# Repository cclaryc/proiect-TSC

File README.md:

# Overview - Hector Watch

Proiectul **Hector Watch** vizează dezvoltarea unui smartwatch, optimizat pentru consum redus de energie. Sistemul este construit în jurul microcontrolerului **nRF52840** și utilizează un afișaj de tip **e-Paper** de 1.54 inch.

### 1. Arhitectura Hardware și Selecția Componentelor
Această etapă a constat în definirea specificațiilor și alegerea componentelor pentru eficiență energetică maximă:
* **Unitate centrală:** nRF52840 (SoC cu suport BLE 5.3).
* **Afișaj:** Panou E-Ink Waveshare 1.54".
* **Senzori și Feedback:** Accelerometru Bosch BMA423 (I2C) și driver haptic TI DRV2605.
* **Sursă de energie:** Baterie Li-Po 250mAh .

## Functional Architecture

Arhitectura funcțională este proiectată pentru a maximiza eficiența energetică și a asigura o comunicare fluidă între procesorul central și perifericele specializate.

### 1. Sistemul de Management al Energiei (PMU)
Acest subsistem asigură alimentarea continuă și protecția circuitelor:
* **Input:** USB-C (5V) pentru încărcare.
* **Încărcare și Protecție:** Realizată prin IC1 , care gestionează ciclul de încărcare al bateriei Li-Po.
* **Monitorizare (Fuel Gauge): U3 raportează starea de încărcare (SoC) și tensiunea bateriei prin I2C.
* **Reglare:** IC2 (Buck-Boost) transformă tensiunea variabilă a bateriei într-o tensiune stabilă de **3.3V** pentru restul componentelor.

### 2. Procesare și Conectivitate
* **Core:** **nRF52840** (ARM Cortex-M4F) rulează logica ceasului și gestionează stack-ul de Bluetooth Low Energy (BLE).
* **Timing:** Cristale externe de 32MHz (precizie procesor) și 32.768kHz (precizie ceas/RTC în mod sleep).

### 3. Interfața Om-Mașină (HMI)
* **Output Vizual:** Ecranul **E-Ink** (cerneală electronică) reține imaginea fără consum de curent, fiind actualizat prin protocolul **SPI**. 
* **Output Haptic:** Driver-ul U2 traduce comenzile I2C în vibrații mecanice prin motorul de tip coin.
* **Input:** Trei butoane fizice (GPIO) pentru navigare și interacțiune.

### 4. Subsistemul de Senzori
* Accelerometrul **BMA423** monitorizează activitatea fizică și detectează orientarea încheieturii pentru activarea ecranului.

### Block Diagram

### Matricea de Comunicație (Data Bus)

| Bus | Periferic | Tip | Rol |
| :--- | :--- | :--- | :--- |
| **SPI** | E-Paper Display | Master -> Slave | Transfer rapid de buffere de imagine |
| **I2C** | BMA423, DRV2605, MAX17048, BQ25180 | Multimaster | Configurare senzori și citire telemetrie baterie |
| **GPIO** | Butoane, Display Power (PFET), Motor EN | Digital I/O | Control direct și evenimente asincrone |

### Bill of Materials

| Referință | Componentă | Funcție | Package | JLC Code | Datasheet |
| :--- | :--- | :--- | :--- | :--- | :--- |
| **IC1 (U1)** | nRF52840-QIAA | Procesor principal (MCU) și controller Bluetooth. | aQFN73 | C190740 | [Link](https://jlcpcb.com/api/file/downloadByFileSystemAccessId/8588884082339532800) |
| **IC2 (U2)** | BQ25180YBGR | Încărcător de baterie inteligent. | WLCSP-8 | C2907431 | [Link](https://www.ti.com/cn/lit/gpn/bq25180) |
| **IC3 (U3)** | MAX17048G+T10 | Monitorizează nivelul bateriei (Fuel Gauge). | TDFN-8 | C72035 | [Link](https://jlc-prod-smt.oss-eu-central-1.aliyuncs.com/smtDataManualFile/8588907428515614720-C2682616.pdf?response-content-disposition=attachment%3B%20filename%3DC2682616.pdf%3B%20filename%2A%3DUTF-8%27%27C2682616.pdf&x-oss-date=20260421T112544Z&x-oss-expires=1800&x-oss-security-token=CAISgAN1q6Ft5B2yfSjIr5n4OcKMmaVj5%2FfYekzrr2IHQf9m3ZfGjzz2IHhMdHJsAOodtv0%2FmmhT6PkclqRLcbhpcmfjV%2BZHzLB8qcVSq2Ny4J7b16cNrbH4M4H6aXeirtuwDsz9SNTCALjPD3nPii50x5bjaDymRCbLGJaViJlhHLN1Ow6jdmhpCctxLAlvo9NgFxm3D%2Fu2NQPwiWf9FVdhvhEG6Vly8qOi2MaRmFy8yFTx0b0SvJ%2BjYMrmPctoN9JnSdC5mfdzau3a1TJ84gRD0a5wkaVA1zbDs5bfISEIuUzebreLqY03dV4mOvdqIcMe8qigz88fk%2FfIioH6xyxKOexoSCnFTOiiupCcQLPyao9jLu6iayqViY7QaIOTqQohZmkAMwVOasAsI3Ngh4zF97Qt0cVNkXO9gWfLI8DtuMleWqrqV%2FhfznSgc5lCkRRYwGs1287ugXlSQzo890KPDAEovaKCnZ2ZSfh7Y4sNknI6i%2Bfc2Se2MIkIzFMa4qKWD5sagAGLzp3fHP9zsDxV2%2FJMGJhYD%2FSIjxpKz7fqt2nFmhY%2BY1WslVCo8Aeg8t%2FASS7YFDik2EKmA7r2Qpp7S9DhCxHh3UmkIh5jq2t2qTGkqx1qYPq5E3JFwFQNyBq2LNYj5F%2B%2BlRwX66i2djJKGm9qTW%2FuuXCYOKChaO82y5rYRjpzLyAA&x-oss-signature-version=OSS4-HMAC-SHA256&x-oss-credential=STS.NZMrx8tzBP53xjZKbRMpJ2Rmm%2F20260421%2Feu-central-1%2Foss%2Faliyun_v4_request&x-oss-signature=e0bf51dc5869d52ac2c81a85deb4332a4d147174e99a754ec8a8e7ac85831cb3) |
| **IC4 (U4)** | DRV2605YZFR | Driver specializat pentru efecte haptice. | BGA-9 | C156475 | [Link](https://www.ti.com/cn/lit/gpn/drv2605) |
| **IC5 (U5)** | BMA423 | Senzor de mișcare (pași/gesturi). | LGA-12 | C406450 | [Link](https://jlc-prod-smt.oss-eu-central-1.aliyuncs.com/smtDataManualFile/8588894317138628608-C189517.pdf?response-content-disposition=attachment%3B%20filename%3DC189517.pdf%3B%20filename%2A%3DUTF-8%27%27C189517.pdf&x-oss-date=20260421T112629Z&x-oss-expires=1800&x-oss-security-token=CAISgAN1q6Ft5B2yfSjIr5n4OcKMmaVj5%2FfYekzrr2IHQf9m3ZfGjzz2IHhMdHJsAOodtv0%2FmmhT6PkclqRLcbhpcmfjV%2BZHzLB8qcVSq2Ny4J7b16cNrbH4M4H6aXeirtuwDsz9SNTCALjPD3nPii50x5bjaDymRCbLGJaViJlhHLN1Ow6jdmhpCctxLAlvo9NgFxm3D%2Fu2NQPwiWf9FVdhvhEG6Vly8qOi2MaRmFy8yFTx0b0SvJ%2BjYMrmPctoN9JnSdC5mfdzau3a1TJ84gRD0a5wkaVA1zbDs5bfISEIuUzebreLqY03dV4mOvdqIcMe8qigz88fk%2FfIioH6xyxKOexoSCnFTOiiupCcQLPyao9jLu6iayqViY7QaIOTqQohZmkAMwVOasAsI3Ngh4zF97Qt0cVNkXO9gWfLI8DtuMleWqrqV%2FhfznSgc5lCkRRYwGs1287ugXlSQzo890KPDAEovaKCnZ2ZSfh7Y4sNknI6i%2Bfc2Se2MIkIzFMa4qKWD5sagAGLzp3fHP9zsDxV2%2FJMGJhYD%2FSIjxpKz7fqt2nFmhY%2BY1WslVCo8Aeg8t%2FASS7YFDik2EKmA7r2Qpp7S9DhCxHh3UmkIh5jq2t2qTGkqx1qYPq5E3JFwFQNyBq2LNYj5F%2B%2BlRwX66i2djJKGm9qTW%2FuuXCYOKChaO82y5rYRjpzLyAA&x-oss-signature-version=OSS4-HMAC-SHA256&x-oss-credential=STS.NZMrx8tzBP53xjZKbRMpJ2Rmm%2F20260421%2Feu-central-1%2Foss%2Faliyun_v4_request&x-oss-signature=1b2c6936aa63600c7496d9337576edecc9ae5bf56b8ef562c67036a6727a361c) |
| **IC6 (U6)** | RT6160AWSC | Regulator Buck-Boost (3.3V stabil). | WLCSP-15 | C141692 | [Link](https://jlcpcb.com/api/file/downloadByFileSystemAccessId/8600398231234883584) |
| **IC7 (U7)** | USBLC6-2SC6Y | Protecție ESD la mufa USB. | SOT-23-6L | C7519 | [Link](https://jlc-prod-smt.oss-eu-central-1.aliyuncs.com/smtDataManualFile/8603165824283140096-C2969755.pdf?response-content-disposition=attachment%3B%20filename%3DC2969755.pdf%3B%20filename%2A%3DUTF-8%27%27C2969755.pdf&x-oss-date=20260421T112712Z&x-oss-expires=1800&x-oss-security-token=CAISgAN1q6Ft5B2yfSjIr5n4OcKMmaVj5%2FfYekzrr2IHQf9m3ZfGjzz2IHhMdHJsAOodtv0%2FmmhT6PkclqRLcbhpcmfjV%2BZHzLB8qcVSq2Ny4J7b16cNrbH4M4H6aXeirtuwDsz9SNTCALjPD3nPii50x5bjaDymRCbLGJaViJlhHLN1Ow6jdmhpCctxLAlvo9NgFxm3D%2Fu2NQPwiWf9FVdhvhEG6Vly8qOi2MaRmFy8yFTx0b0SvJ%2BjYMrmPctoN9JnSdC5mfdzau3a1TJ84gRD0a5wkaVA1zbDs5bfISEIuUzebreLqY03dV4mOvdqIcMe8qigz88fk%2FfIioH6xyxKOexoSCnFTOiiupCcQLPyao9jLu6iayqViY7QaIOTqQohZmkAMwVOasAsI3Ngh4zF97Qt0cVNkXO9gWfLI8DtuMleWqrqV%2FhfznSgc5lCkRRYwGs1287ugXlSQzo890KPDAEovaKCnZ2ZSfh7Y4sNknI6i%2Bfc2Se2MIkIzFMa4qKWD5sagAGLzp3fHP9zsDxV2%2FJMGJhYD%2FSIjxpKz7fqt2nFmhY%2BY1WslVCo8Aeg8t%2FASS7YFDik2EKmA7r2Qpp7S9DhCxHh3UmkIh5jq2t2qTGkqx1qYPq5E3JFwFQNyBq2LNYj5F%2B%2BlRwX66i2djJKGm9qTW%2FuuXCYOKChaO82y5rYRjpzLyAA&x-oss-signature-version=OSS4-HMAC-SHA256&x-oss-credential=STS.NZMrx8tzBP53xjZKbRMpJ2Rmm%2F20260421%2Feu-central-1%2Foss%2Faliyun_v4_request&x-oss-signature=3bd40d510d9216cc6425f6a729325acb3ecaeffaa7238b5506b9054adb73b786) |
| **X1** | ECS-320-10-33B | Cristal 32MHz pentru Bluetooth. | 3225 SMD | C110292 | [Link](https://www.google.com/search?q=https://ecsxtal.com/store/pdf/ECS-320-10-33B-CKM.pdf) |
| **X2** | NX3215SA | Cristal 32.768kHz pentru RTC. | 3215 SMD | C32156 | [Link](https://www.ndk.com/images/products/catalog/c_NX3215SA_e.pdf) |
| **D1** | MBR0530 | Diodă Schottky pentru protecție curent. | SOD-123 | C8200 | [Link](https://www.onsemi.com/pdf/datasheet/mbr0530t1-d.pdf) |
| **D2-D5** | Generic 0402 | LED-uri stare (încărcare/notificări). | 0402 SMD | - | - |
| **L1** | MLP2016H2R2MT | Inductor Power pentru RT6160. | 2016 SMD | C135431 | [Link](https://product.tdk.com/system/files/dam/doc/product/inductor/inductor/smd/catalog/inductor_commercial_power_mlp2016_en.pdf) |
| **Q1** | SI1308EDL | Switch logic pentru alimentare display. | SOT-23 | C140222 | [Link](https://www.vishay.com/docs/63399/si1308edl.pdf) |
| **Resistors** | C3920633 | Pull-up I2C și limitare LED. | 0201 | **C3920633** | - |
| **Capacitors**| C9900156064 | Filtrare și decuplare generală. | 0201 | **C9900156064** | - |
| **C23, 27..** | C21012218 | Stabilitate tensiune. | - | **C21012218** | - |
| **C24, 25..** | C9900179830 | Filtrare intrare/ieșire putere. | 0402 | **C9900179830** | - |
| **DISP** | Waveshare 1.54" | Ecran principal E-Ink. | 37.3x31.8 mm | - | [Link PDF](https://www.waveshare.com/w/upload/7/77/1.54inch_e-Paper_Datasheet.pdf?srsltid=AfmBOorvr9QUc2F2yPCG9JTKScM4Ca_KRrmOvzZPdTIs-fBF9CH1EZh_) |
| **BATT** | Akyga LP502030 | Sursă energie (250mAh). | 32.5x21 mm | - | [Link](https://files.elektroniksc.com.pl/14017-2427914986/LP502030.pdf) |
| **MOT** | FIT0774 | Motor vibrații haptic. | Ø10 x 3 mm | - | [Link](https://jlc-prod-smt.oss-eu-central-1.aliyuncs.com/smtDataManualFile/8600542373223424000-C17569954.pdf?response-content-disposition=attachment%3B%20filename%3DC17569954.pdf%3B%20filename%2A%3DUTF-8%27%27C17569954.pdf&x-oss-date=20260421T113148Z&x-oss-expires=1800&x-oss-security-token=CAISgAN1q6Ft5B2yfSjIr5n4OcKMmaVj5%2FfYekzrr2IHQf9m3ZfGjzz2IHhMdHJsAOodtv0%2FmmhT6PkclqRLcbhpcmfjV%2BZHzLB8qcVSq2Ny4J7b16cNrbH4M4H6aXeirtuwDsz9SNTCALjPD3nPii50x5bjaDymRCbLGJaViJlhHLN1Ow6jdmhpCctxLAlvo9NgFxm3D%2Fu2NQPwiWf9FVdhvhEG6Vly8qOi2MaRmFy8yFTx0b0SvJ%2BjYMrmPctoN9JnSdC5mfdzau3a1TJ84gRD0a5wkaVA1zbDs5bfISEIuUzebreLqY03dV4mOvdqIcMe8qigz88fk%2FfIioH6xyxKOexoSCnFTOiiupCcQLPyao9jLu6iayqViY7QaIOTqQohZmkAMwVOasAsI3Ngh4zF97Qt0cVNkXO9gWfLI8DtuMleWqrqV%2FhfznSgc5lCkRRYwGs1287ugXlSQzo890KPDAEovaKCnZ2ZSfh7Y4sNknI6i%2Bfc2Se2MIkIzFMa4qKWD5sagAGLzp3fHP9zsDxV2%2FJMGJhYD%2FSIjxpKz7fqt2nFmhY%2BY1WslVCo8Aeg8t%2FASS7YFDik2EKmA7r2Qpp7S9DhCxHh3UmkIh5jq2t2qTGkqx1qYPq5E3JFwFQNyBq2LNYj5F%2B%2BlRwX66i2djJKGm9qTW%2FuuXCYOKChaO82y5rYRjpzLyAA&x-oss-signature-version=OSS4-HMAC-SHA256&x-oss-credential=STS.NZMrx8tzBP53xjZKbRMpJ2Rmm%2F20260421%2Feu-central-1%2Foss%2Faliyun_v4_request&x-oss-signature=3123648a1255a4bcd5d4fe98690891d424c0b7d99660a32dc277129baedf181c) |
| **USB** | KH-TYPE-C-16P | Port încărcare și date USB-C. | 16-pin SMD | C165948 | [Link](https://www.snapeda.com/parts/KH-TYPE-C-16P/kinghelm/datasheet/) |
| **J1** | 503480-2400 | Conector FPC (Display). | 0.5mm Pitch | C262524 | [Link](https://www.molex.com/en-us/products/part-detail/5034802400) |
| **ANT** | 2450AT18B100E | Antenă Bluetooth 2.4GHz. | 3216 SMD | C105151 | [Link](https://www.johansontechnology.com/datasheets/2450AT18B100.pdf) |
| **BTN** | EVP-AKE31A | Butoane navigare meniu. | 3.8x1.9 mm | C138127 | [Link](hhttps://jlc-prod-smt.oss-eu-central-1.aliyuncs.com/smtDataManualFile/8588931144787611648-C569760.pdf?response-content-disposition=attachment%3B%20filename%3DC569760.pdf%3B%20filename%2A%3DUTF-8%27%27C569760.pdf&x-oss-date=20260421T113342Z&x-oss-expires=1800&x-oss-security-token=CAISgAN1q6Ft5B2yfSjIr5n4OcKMmaVj5%2FfYekzrr2IHQf9m3ZfGjzz2IHhMdHJsAOodtv0%2FmmhT6PkclqRLcbhpcmfjV%2BZHzLB8qcVSq2Ny4J7b16cNrbH4M4H6aXeirtuwDsz9SNTCALjPD3nPii50x5bjaDymRCbLGJaViJlhHLN1Ow6jdmhpCctxLAlvo9NgFxm3D%2Fu2NQPwiWf9FVdhvhEG6Vly8qOi2MaRmFy8yFTx0b0SvJ%2BjYMrmPctoN9JnSdC5mfdzau3a1TJ84gRD0a5wkaVA1zbDs5bfISEIuUzebreLqY03dV4mOvdqIcMe8qigz88fk%2FfIioH6xyxKOexoSCnFTOiiupCcQLPyao9jLu6iayqViY7QaIOTqQohZmkAMwVOasAsI3Ngh4zF97Qt0cVNkXO9gWfLI8DtuMleWqrqV%2FhfznSgc5lCkRRYwGs1287ugXlSQzo890KPDAEovaKCnZ2ZSfh7Y4sNknI6i%2Bfc2Se2MIkIzFMa4qKWD5sagAGLzp3fHP9zsDxV2%2FJMGJhYD%2FSIjxpKz7fqt2nFmhY%2BY1WslVCo8Aeg8t%2FASS7YFDik2EKmA7r2Qpp7S9DhCxHh3UmkIh5jq2t2qTGkqx1qYPq5E3JFwFQNyBq2LNYj5F%2B%2BlRwX66i2djJKGm9qTW%2FuuXCYOKChaO82y5rYRjpzLyAA&x-oss-signature-version=OSS4-HMAC-SHA256&x-oss-credential=STS.NZMrx8tzBP53xjZKbRMpJ2Rmm%2F20260421%2Feu-central-1%2Foss%2Faliyun_v4_request&x-oss-signature=de82d2c18fd97c4e0818f889d880a6cdc2a8298c582eb4e00e03563dc11a3a5e) |
| **PROG** | TC2030-IDC | Interfață programare (Tag-Connect). | Plug-of-Nails | - | [Link](https://www.snapeda.com/parts/TC2030-IDC/Tag-Connect%20LLC/datasheet/) |

## nRF52840 Pin Mapping

### 1. Magistrala I2C (Senzori și Management Energie)
Această magistrală este utilizată pentru comunicarea cu majoritatea componentelor inteligente din sistem.
* **P0.26:** Linia de date **SDA**. Conectează:
    * **IC1** (Charger BQ25180)
    * **IC3** (IMU BMA421)
    * **U3** (Fuel Gauge MAX17048)
    * **IC2** (Haptic Driver DRV2605)
* **P0.27:** Linia de ceas **SCL**

### 2. Interfața SPI și Control (E-Paper Display)
Conexiunile către conectorul **J1** (E-Paper Display Connector)
* **P0.05:** EPD_SCK (Ceas SPI).
* **P0.07:** EPD_MOSI (Date SPI)
* **P0.12:** EPD_CS (Chip Select)
* **P0.11:** EPD_DC (Data/Command control)
* **P0.04:** EPD_RST (Reset Display).
* **P0.08:** EPD_BUSY (Semnal stare display).
* **P0.31:** **PWR_EPD_CTRL** – Controlează tranzistorul **Q1** pentru a activa/dezactiva alimentarea întregului circuit de display

### 3. Interfață Utilizator (Butoane și Haptic)
* **P1.00:** Buton **SW_UP**
* **P1.01:** Buton **SW_ENT** (Enter/Select)
* **P1.02:** Buton **SW_DN** (Down)
* **P0.29:** **HAPTIC_EN / INTRIG** – Pinul de declanșare pentru driverul de vibrații **IC2**

### 4. Sistem și Debug
* **P0.18 / RESET:** Pinul de reset hardware, conectat la interfața de programare.
* **SWDIO / SWCLK:** Pinii de programare și depanare prin interfața **SWD**, conectați la mufa **TC2030**
* **ANT:** Pinul dedicat pentru ieșirea radio, conectat la antena chip de 2.4GHz (**ANT1**)

### 5. Alimentare (Power Rails)
* **VDD / VDDH:** Alimentarea principală de **3.3V** provenită de la regulatorul DC/DC
* **VSS:** Conexiunile la masă (**GND**)

## Design Considerations
* **Componente doar pe TOP:** Toate piesele sunt pe o singură față pentru asamblare rapidă și ieftină.
* **Plane de GND:** Cupru pe ambele părți pentru protecție și semnal fără zgomot.
* **Via stitching:** Găuri multe lângă antenă pentru a bloca interferențele radio.
* **Decuplare:** Condensatori puși fix lângă pini pentru un curent cât mai stabil.
* **Keepout antenă:** Zonă fără cupru sub antenă pentru semnal Bluetooth maxim.
* **Baterie fără JST:** Baterie lipită direct, fără mufă, pentru a face ceasul cât mai subțire.

## Design Rule Check (DRC) Exceptions
| Tip eroare                         | Componentă                            | Explicație simplă                                                                                  |
| ---------------------------------- | ------------------------------------- | -------------------------------------------------------------------------------------------------- |
| Solid Polygon Shape - Pad Overlap  | Butoane tactile / planuri de cupru    | Suprapunerea este din cauza amplasarii butoanelor.                                                 |
| SMD-Via Overlap                    | nRF52840 (CPU)                        | Via-in-pad este necesar la acest procesor, fiindcă are pini mulți și spațiu foarte mic.            |
| Wire Copper Width                  | Trasee de putere / intrări componente | Traseele se îngustează local ca să poată intra între pini fără să facă scurt.  [necking]           |
| Wire/Via Copper Clearance          | Rutare internă CPU                    | Distanțele sunt mai mici din lipsă de spațiu, dar sunt încă în limitele acceptate de fabricație.   |
| SMD-Hole / Board Outline Clearance | USB Type-C / margine PCB              | Conectorul USB-C este pus aproape de margine pentru a se potrivi corect cu decupajul carcasei.     |

## Hardware Renderings & Visuals
### Final PCB Layout

### Final Design Render

### Final Design Explored

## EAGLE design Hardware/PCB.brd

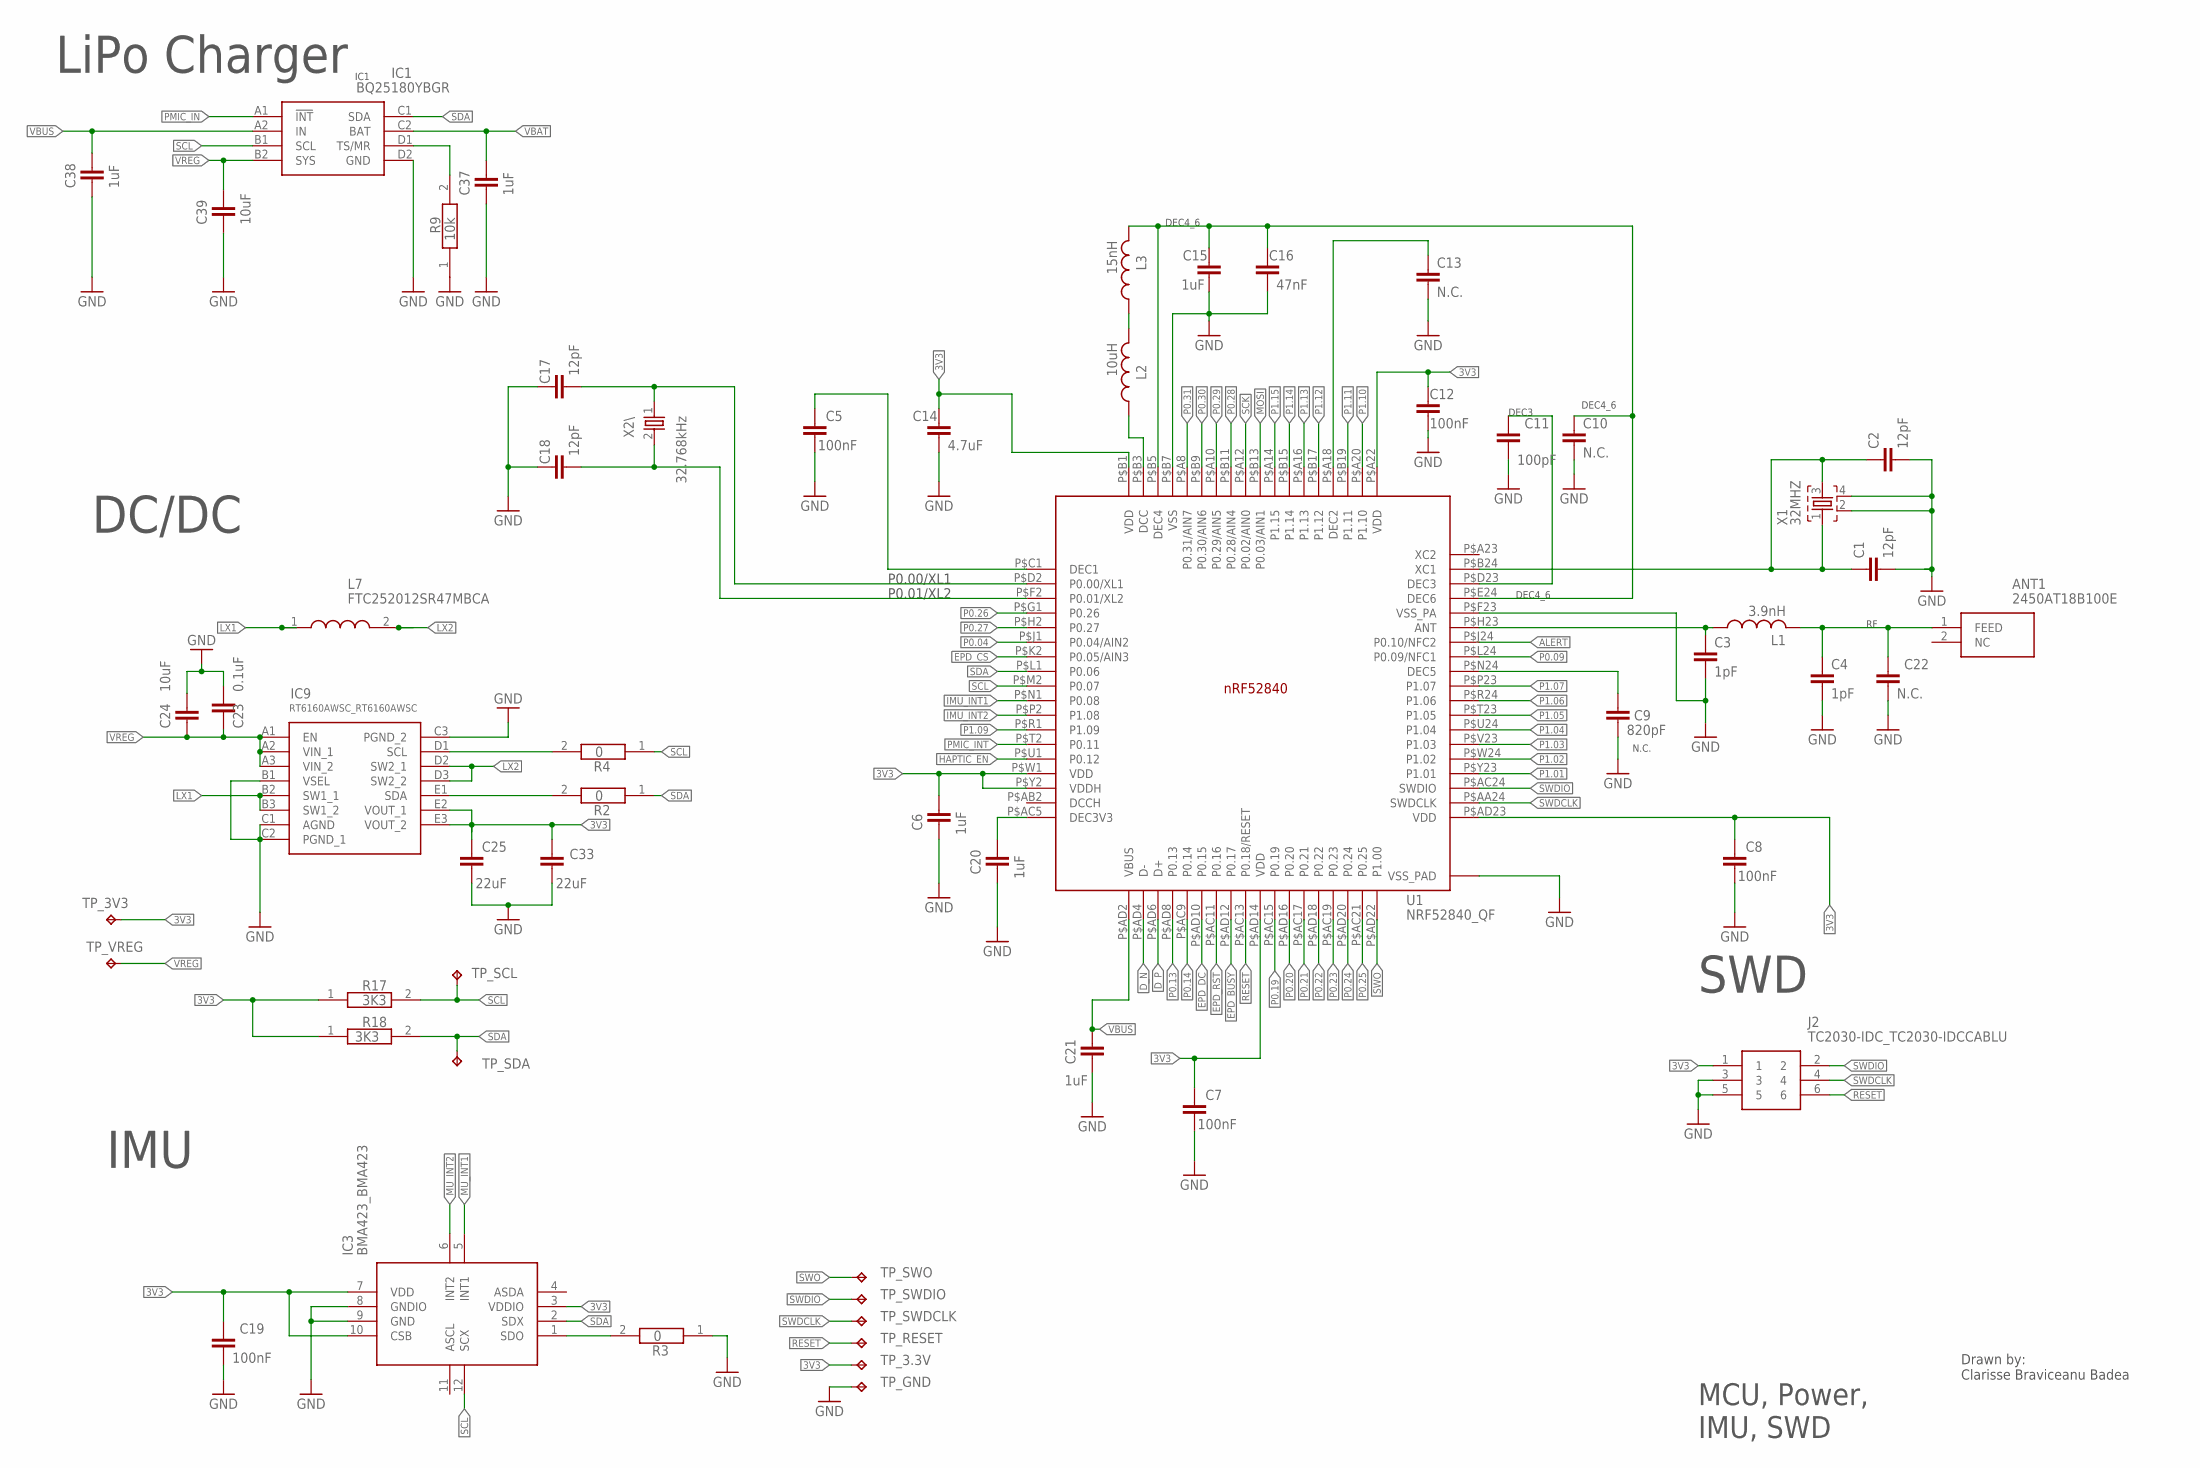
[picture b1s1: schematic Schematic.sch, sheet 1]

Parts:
ANT1: 2450AT18B100E; 2450AT18B100E_ANTC3216X140N
C1, C2, C17, C18: 12pF; NORDIC_NRF_3_RESC0201_N
C3, C4: 1pF; NORDIC_NRF_3_RESC0201_N
C5, C7, C8, C12, C19: 100nF; NORDIC_NRF_3_RESC0201_N
C6, C15, C20, C21, C37, C38: 1uF; NORDIC_NRF_3_RESC0402_N
C9: 820pF; NORDIC_NRF_3_RESC0201_N
C10, C13, C22: N.C.; NORDIC_NRF_3_RESC0201_N
C11: 100pF; NORDIC_NRF_3_RESC0201_N
C14: 4.7uF; NORDIC_NRF_3_RESC0402_N
C16: 47nF; NORDIC_NRF_3_RESC0201_N
C23: 0.1uF; NORDIC_NRF_3_RESC0201_N
C24, C39: 10uF; NORDIC_NRF_3_RESC0402_N
C25, C33: 22uF; NORDIC_NRF_3_RESC0402_N
IC1: BQ25180YBGR; BQ25180YBGR_BGA8C40P2X4_100X155X50
IC3: BMA423_BMA423
IC9: RT6160AWSC_RT6160AWSC; RT6160AWSC_BGA15C40P3X5_140X230X60
J2: TC2030-IDC_TC2030-IDCCABLU; TC2030-IDC_TC2030IDC
L1: 3.9nH; NORDIC_NRF_2_RESC0402_L
L2: 10uH; NORDIC_NRF_2_RESC0402_L
L3: 15nH; NORDIC_NRF_2_RESC0402_L
L7: FTC252012SR47MBCA; MLP2016SR47MT0S1_INDC2016X100N
R2, R3, R4: 0; CPF0201D7K68C1_0201
R9: 10k; CPF0201D7K68C1_0201
R17, R18: 3K3; CPF0201D7K68C1_0201
TP_3.3V, TP_3V3: HECTOR_WATCH_1_TPTP20R; HECTOR_WATCH_1_TP20R
TP_GND: HECTOR_WATCH_1_TPTP20R; HECTOR_WATCH_1_TP20R
TP_RESET: HECTOR_WATCH_1_TPTP20R; HECTOR_WATCH_1_TP20R
TP_SCL: HECTOR_WATCH_1_TPTP20R; HECTOR_WATCH_1_TP20R
TP_SDA: HECTOR_WATCH_1_TPTP20R; HECTOR_WATCH_1_TP20R
TP_SWDCLK: HECTOR_WATCH_1_TPTP20R; HECTOR_WATCH_1_TP20R
TP_SWDIO: HECTOR_WATCH_1_TPTP20R; HECTOR_WATCH_1_TP20R
TP_SWO: HECTOR_WATCH_1_TPTP20R; HECTOR_WATCH_1_TP20R
TP_VREG: HECTOR_WATCH_1_TPTP20R; HECTOR_WATCH_1_TP20R
U1: NRF52840_QF; NORDIC_NRF_4_AQFN50P700X700X85_HS-74N
X1: 32MHZ; NORDIC_NRF_BT-XTAL_2016_N
X2\: 32.768kHz; NORDIC_NRF_1_XTAL_3215_N

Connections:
3V3: C6.1, C7.1, C8.1, C12.2, C14.1, C19.2, C25.1, C33.1, IC3.3 (VDDIO), IC3.7 (VDD), IC3.10 (CSB), IC9.E2 (VOUT_1), IC9.E3 (VOUT_2), J2.1, R17.1, R18.1, TP_3.3V.TP, TP_3V3.TP, U1.P$A22 (VDD), U1.P$AD14 (VDD), U1.P$AD23 (VDD), U1.P$B1 (VDD), U1.P$W1 (VDD), U1.P$Y2 (VDDH); also elsewhere on the board
ALERT: U1.P$J24 (P0.10/NFC2); also elsewhere on the board
D_N: U1.P$AD4 (D-); also elsewhere on the board
D_P: U1.P$AD6 (D+); also elsewhere on the board
EPD_BUSY: U1.P$AD12 (P0.17); also elsewhere on the board
EPD_CS: U1.P$K2 (P0.05/AIN3); also elsewhere on the board
EPD_DC: U1.P$AD10 (P0.15); also elsewhere on the board
EPD_RST: U1.P$AC11 (P0.16); also elsewhere on the board
GND: C1.2, C2.2, C3.1, C4.1, C5.2, C6.2, C7.2, C8.2, C9.1, C10.1, C11.1, C12.1, C13.1, C14.2, C15.2, C16.1, C17.1, C18.1, C19.1, C20.2, C21.2, C22.1, C23.1, C24.1, C25.2, C33.2, C37.2, C38.2, C39.2, IC1.D2 (GND), IC3.8 (GNDIO), IC3.9 (GND), IC9.B1 (VSEL), IC9.C1 (AGND), IC9.C2 (PGND_1), IC9.C3 (PGND_2), J2.3, J2.5, R3.1, R9.1, TP_GND.TP, U1.P$74 (VSS_PAD), U1.P$75 (VSS_PAD), U1.P$76 (VSS_PAD), U1.P$77 (VSS_PAD), U1.P$78 (VSS_PAD), U1.P$79 (VSS_PAD), U1.P$80 (VSS_PAD), U1.P$81 (VSS_PAD), U1.P$82 (VSS_PAD), U1.P$83 (VSS_PAD), U1.P$84 (VSS_PAD), U1.P$85 (VSS_PAD), U1.P$86 (VSS_PAD), U1.P$87 (VSS_PAD), U1.P$88 (VSS_PAD), U1.P$89 (VSS_PAD), U1.P$90 (VSS_PAD), U1.P$B7 (VSS), U1.P$F23 (VSS_PA), X1.2, X1.4; also elsewhere on the board
HAPTIC_EN: U1.P$U1 (P0.12); also elsewhere on the board
IMU_INT1: U1.P$N1 (P0.08)
IMU_INT2: U1.P$P2 (P1.08)
LX1: IC9.B2 (SW1_1), IC9.B3 (SW1_2), L7.1
LX2: IC9.D2 (SW2_1), IC9.D3 (SW2_2), L7.2
MOSI: U1.P$B13 (P0.03/AIN1); also elsewhere on the board
MU_INT1: IC3.5 (INT1)
MU_INT2: IC3.6 (INT2)
unnamed: C3.2, L1.1, U1.P$H23 (ANT)
unnamed: ANT1.1 (FEED), C4.2, C22.2, L1.2
unnamed: C11.2, U1.P$D23 (DEC3)
unnamed: C1.1, C2.1, U1.P$B24 (XC1), X1.1, X1.3
unnamed: C9.2, U1.P$N24 (DEC5)
unnamed: L2.1, U1.P$B3 (DCC)
unnamed: IC1.D1 (TS/MR), R9.2
unnamed: IC9.D1 (SCL), R4.2
unnamed: IC9.E1 (SDA), R2.2
unnamed: IC3.1 (SDO), R3.2
unnamed: C5.1, U1.P$C1 (DEC1)
unnamed: C17.2, U1.P$D2 (P0.00/XL1), X2\.1
unnamed: C20.1, U1.P$AC5 (DEC3V3)
unnamed: C18.2, U1.P$F2 (P0.01/XL2), X2\.2
unnamed: L2.2, L3.1
unnamed: C10.2, C15.1, C16.2, L3.2, U1.P$B5 (DEC4), U1.P$E24 (DEC6)
unnamed: C13.2, U1.P$A18 (DEC2)
P0.04: U1.P$J1 (P0.04/AIN2)
P0.09: U1.P$L24 (P0.09/NFC1)
P0.13: U1.P$AD8 (P0.13); also elsewhere on the board
P0.14: U1.P$AC9 (P0.14); also elsewhere on the board
P0.19: U1.P$AC15 (P0.19)
P0.20: U1.P$AD16 (P0.20)
P0.21: U1.P$AC17 (P0.21)
P0.22: U1.P$AD18 (P0.22)
P0.23: U1.P$AC19 (P0.23)
P0.24: U1.P$AD20 (P0.24)
P0.25: U1.P$AC21 (P0.25)
P0.26: U1.P$G1 (P0.26)
P0.27: U1.P$H2 (P0.27)
P0.28: U1.P$B11 (P0.28/AIN4)
P0.29: U1.P$A10 (P0.29/AIN5)
P0.30: U1.P$B9 (P0.30/AIN6)
P0.31: U1.P$A8 (P0.31/AIN7)
P1.01: U1.P$Y23 (P1.01); also elsewhere on the board
P1.02: U1.P$W24 (P1.02); also elsewhere on the board
P1.03: U1.P$V23 (P1.03)
P1.04: U1.P$U24 (P1.04)
P1.05: U1.P$T23 (P1.05)
P1.06: U1.P$R24 (P1.06)
P1.07: U1.P$P23 (P1.07)
P1.09: U1.P$R1 (P1.09)
P1.10: U1.P$A20 (P1.10)
P1.11: U1.P$B19 (P1.11)
P1.12: U1.P$B17 (P1.12)
P1.13: U1.P$A16 (P1.13)
P1.14: U1.P$B15 (P1.14)
P1.15: U1.P$A14 (P1.15)
PMIC_IN: IC1.A1 (!INT)
PMIC_INT: U1.P$T2 (P0.11)
RESET: J2.6, TP_RESET.TP, U1.P$AC13 (P0.18/RESET)
SCK: U1.P$A12 (P0.02/AIN0); also elsewhere on the board
SCL: IC1.B1 (SCL), IC3.12 (SCX), R4.1, R17.2, TP_SCL.TP, U1.P$M2 (P0.07); also elsewhere on the board
SDA: IC1.C1 (SDA), IC3.2 (SDX), R2.1, R18.2, TP_SDA.TP, U1.P$L1 (P0.06); also elsewhere on the board
SWDCLK: J2.4, TP_SWDCLK.TP, U1.P$AA24 (SWDCLK)
SWDIO: J2.2, TP_SWDIO.TP, U1.P$AC24 (SWDIO)
SWO: TP_SWO.TP, U1.P$AD22 (P1.00)
VBAT: C37.1, IC1.C2 (BAT); also elsewhere on the board
VBUS: C21.1, C38.1, IC1.A2 (IN), U1.P$AD2 (VBUS); also elsewhere on the board
VREG: C23.2, C24.2, C39.1, IC1.B2 (SYS), IC9.A1 (EN), IC9.A2 (VIN_1), IC9.A3 (VIN_2), TP_VREG.TP

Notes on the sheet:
DC/DC
SWD
N.C.
DEC3
DEC4_6
LiPo Charger
IMU
Drawn by: Clarisse Braviceanu Badea
IC1
MCU, Power, IMU, SWD
P0.00/XL1
P0.01/XL2

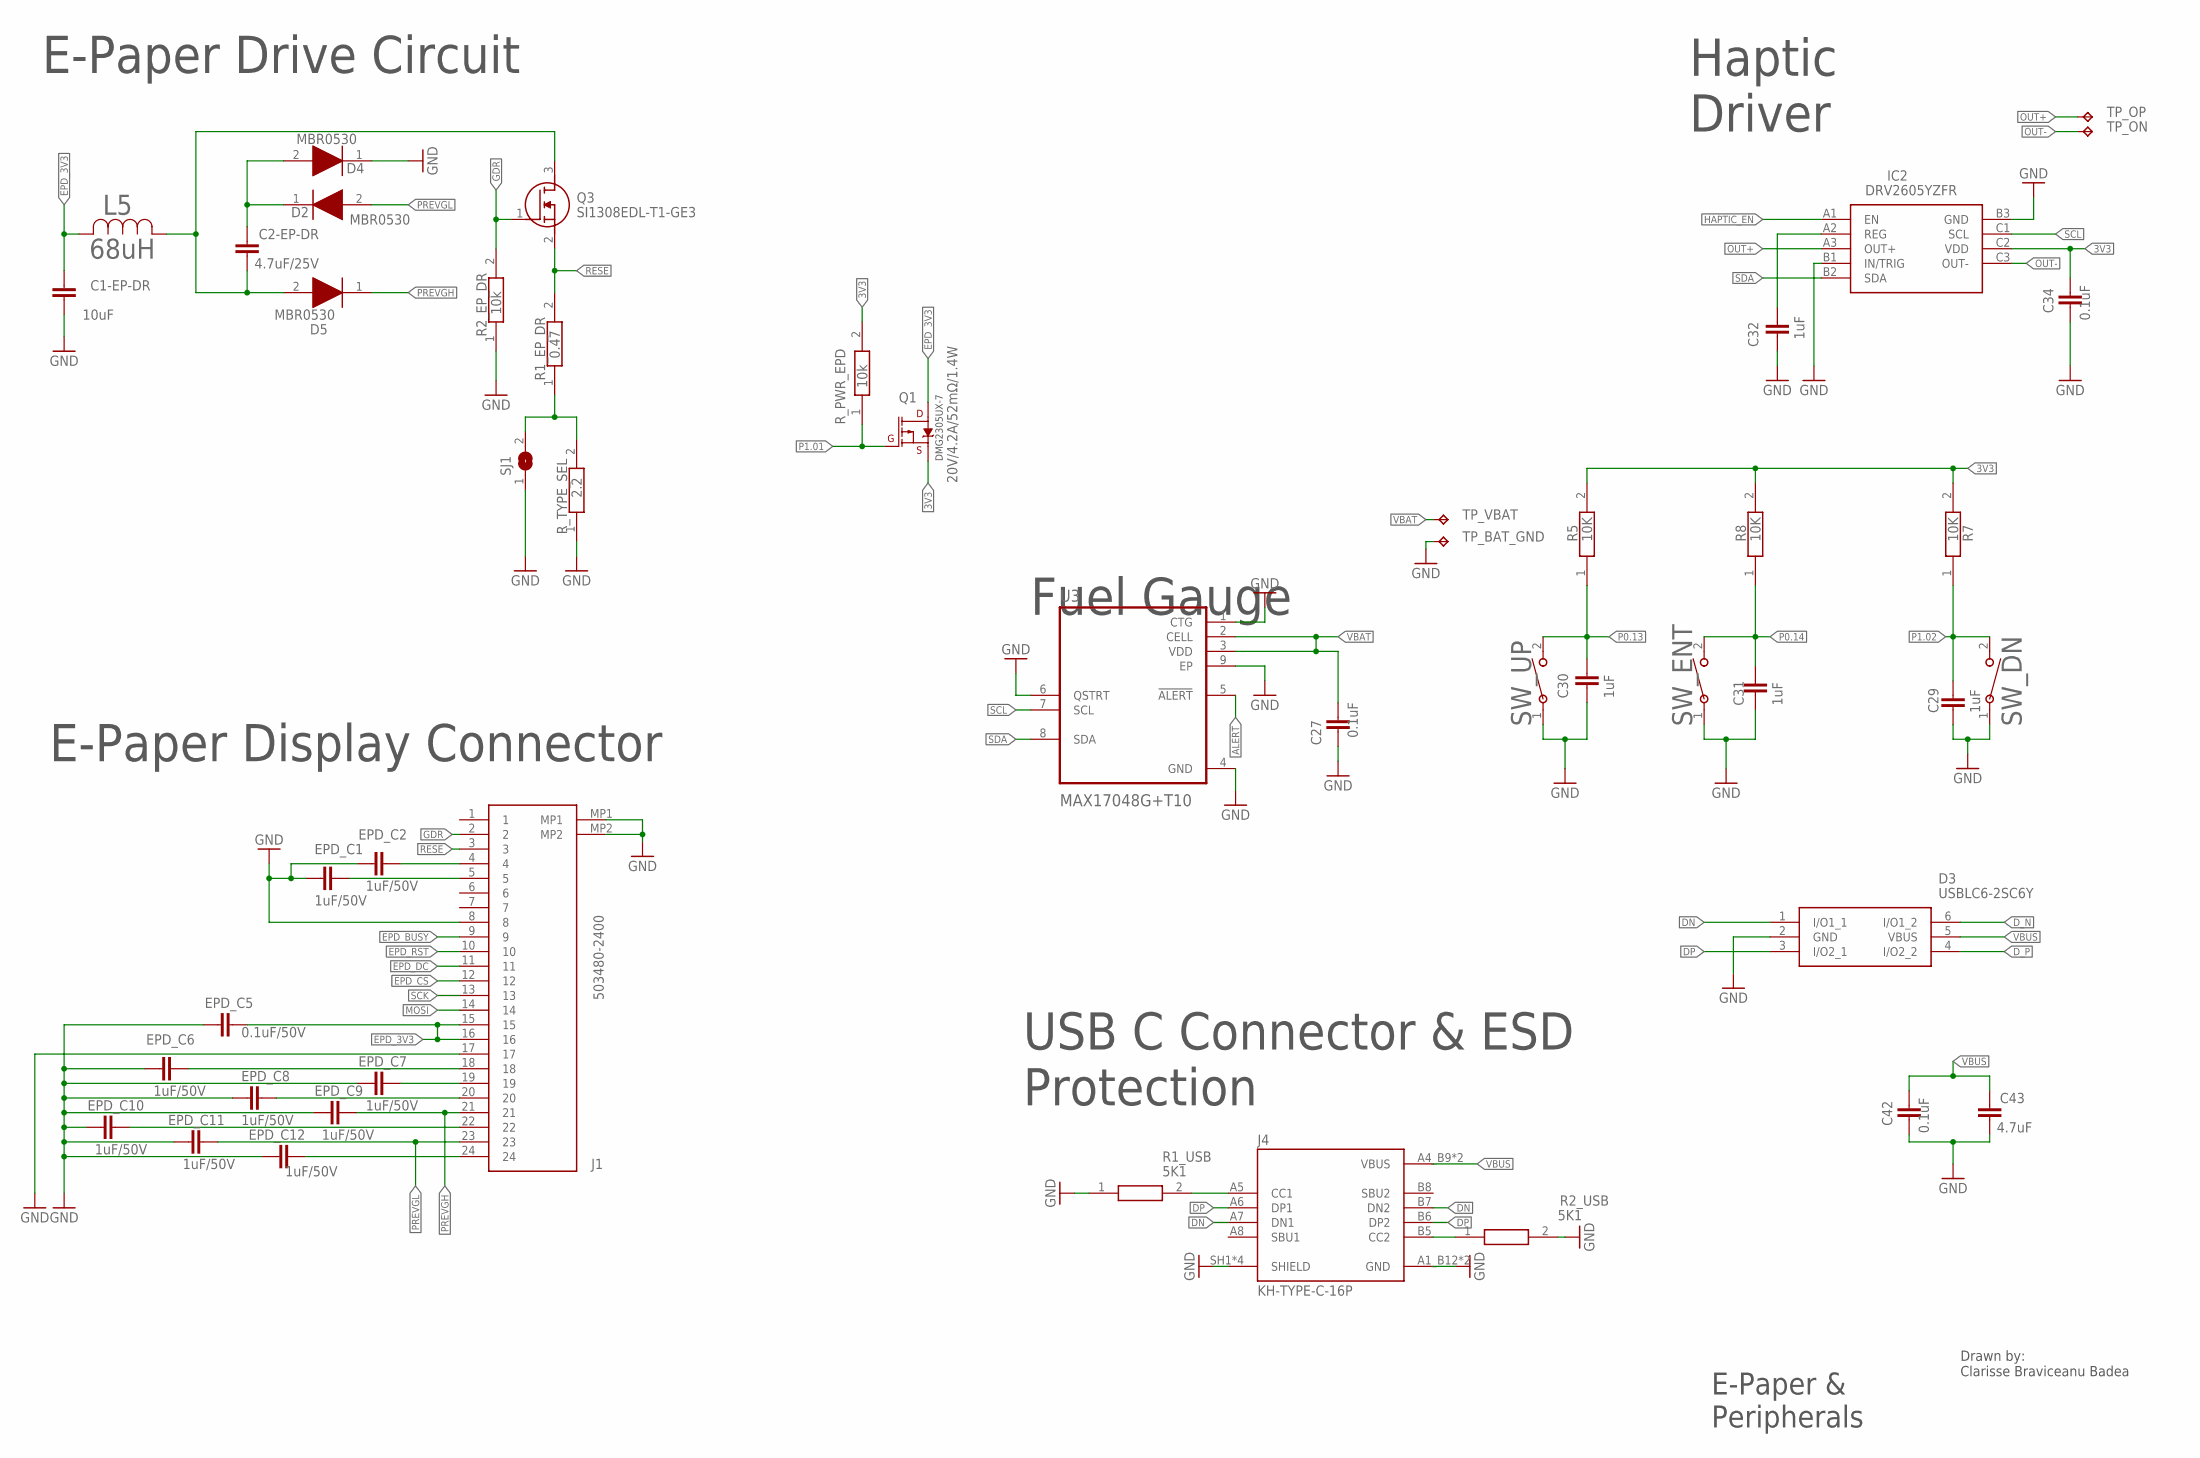
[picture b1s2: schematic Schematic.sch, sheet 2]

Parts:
C1-EP-DR: 10uF; NORDIC_NRF_3_RESC0402_N
C2-EP-DR: 4.7uF/25V; ESP32_C6_LIBRARY_1_ESP32_WROVER_EAGLE-LTSPICE_C0402
C27: 0.1uF; NORDIC_NRF_3_RESC0402_N
C29, C30, C31, C32: 1uF; NORDIC_NRF_3_RESC0402_N
C34, C42: 0.1uF; NORDIC_NRF_3_RESC0201_N
C43: 4.7uF; NORDIC_NRF_3_RESC0402_N
D2, D4, D5: MBR0530; ESP32_C6_LIBRARY_5_SOD3716X135N
D3: USBLC6-2SC6Y; ESP32_C6_LIBRARY_3_SOT95P280X145-6N
EPD_C1, EPD_C2, EPD_C6, EPD_C7, EPD_C8, EPD_C9, EPD_C10, EPD_C11, EPD_C12: 1uF/50V; NORDIC_NRF_3_RESC0402_N
EPD_C5: 0.1uF/50V; NORDIC_NRF_3_RESC0402_N
IC2: DRV2605YZFR; DRV2605YZFR_BGA9C50P3X3_144X144X62
J1: 503480-2400; 503480-2400_5034802400
J4: KH-TYPE-C-16P; KH-TYPE-C-16P_KINGHELM_KH-TYPE-C-16P
L5: 68uH; ESP32_C6_LIBRARY_2_IND_4828-WE-TPC_WRE
Q1: 20V/4.2A/52mΩ/1.4W; ESP32_C6_LIBRARY_4_ESP32_C6_LIBRARY_4_ESP32_C6_LIBRARY_4_ES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
Q3: SI1308EDL-T1-GE3; ESP32_C6_LIBRARY_6_SOT65P210X110-3N
R1_EP_DR: 0.47; CPF0201D7K68C1_0201
R1_USB, R2_USB: 5K1; CPF0201D7K68C1_0201
R2_EP_DR: 10k; CPF0201D7K68C1_0201
R5, R7, R8: 10K; CPF0201D7K68C1_0201
R_PWR_EPD: 10k; CPF0201D7K68C1_0201
R_TYPE_SEL: 2.2; CPF0201D7K68C1_0201
SJ1: ESP32_C6_LIBRARY_7_JUMPER_SJ
SW_DN: 2025-10-22_07-23-44_LIBRARY_EVP-AKE31ASW_EVP-AKE3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; 2025-10-22_07-23-44_LIBRARY_SW_EVP-AKE31A_PAN
SW_ENT: 2025-10-22_07-23-44_LIBRARY_EVP-AKE31ASW_EVP-AKE3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; 2025-10-22_07-23-44_LIBRARY_SW_EVP-AKE31A_PAN
SW_UP: 2025-10-22_07-23-44_LIBRARY_EVP-AKE31ASW_EVP-AKE3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; 2025-10-22_07-23-44_LIBRARY_SW_EVP-AKE31A_PAN
TP_BAT_GND: HECTOR_WATCH_1_TPTP20R; HECTOR_WATCH_1_TP20R
TP_ON: HECTOR_WATCH_1_TPTP20R; HECTOR_WATCH_1_TP20R
TP_OP: HECTOR_WATCH_1_TPTP20R; HECTOR_WATCH_1_TP20R
TP_VBAT: HECTOR_WATCH_1_TPTP20R; HECTOR_WATCH_1_TP20R
U3: MAX17048G+T10; ESP32_C6_LIBRARY_SON50P200X200X80-9N

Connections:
3V3: C34.1, IC2.C2 (VDD), Q1.2 (S), R5.2, R7.2, R8.2, R_PWR_EPD.2; also elsewhere on the board
ALERT: U3.5 (!ALERT); also elsewhere on the board
DN: D3.1 (I/O1_1), J4.A7 (DN1), J4.B7 (DN2)
DP: D3.3 (I/O2_1), J4.A6 (DP1), J4.B6 (DP2)
D_N: D3.6 (I/O1_2); also elsewhere on the board
D_P: D3.4 (I/O2_2); also elsewhere on the board
EPD_3V3: C1-EP-DR.1, EPD_C5.2, J1.15, J1.16, L5.2, Q1.3 (D)
EPD_BUSY: J1.9; also elsewhere on the board
EPD_CS: J1.12; also elsewhere on the board
EPD_DC: J1.11; also elsewhere on the board
EPD_RST: J1.10; also elsewhere on the board
GDR: J1.2, Q3.1 (G), R2_EP_DR.2
GND: C1-EP-DR.2, C27.1, C29.2, C30.1, C31.1, C32.1, C34.2, C42.2, C43.2, D3.2 (GND), D4.1 (K), EPD_C1.1, EPD_C2.1, EPD_C5.1, EPD_C6.1, EPD_C7.1, EPD_C8.1, EPD_C9.1, EPD_C10.1, EPD_C11.1, EPD_C12.1, IC2.B1 (IN/TRIG), IC2.B3 (GND), J1.8, J1.17, J1.MP1, J1.MP2, J4.A1_B12 (GND), J4.A12_B1 (GND), J4.SH1 (SHIELD), J4.SH2 (SHIELD), J4.SH3 (SHIELD), J4.SH4 (SHIELD), R1_USB.1, R2_EP_DR.1, R2_USB.2, R_TYPE_SEL.1, SJ1.1, SW_DN.1, SW_ENT.1, SW_UP.1, TP_BAT_GND.TP, U3.1 (CTG), U3.4 (GND), U3.6 (QSTRT), U3.9 (EP); also elsewhere on the board
HAPTIC_EN: IC2.A1 (EN); also elsewhere on the board
MOSI: J1.14; also elsewhere on the board
unnamed: J4.A5 (CC1), R1_USB.2
unnamed: J4.B5 (CC2), R2_USB.1
unnamed: C2-EP-DR.2, D5.2 (A), L5.1, Q3.3 (D)
unnamed: EPD_C6.2, J1.18
unnamed: EPD_C7.2, J1.19
unnamed: EPD_C8.2, J1.20
unnamed: C2-EP-DR.1, D2.1 (K), D4.2 (A)
unnamed: EPD_C2.2, J1.4
unnamed: EPD_C1.2, J1.5
unnamed: R1_EP_DR.1, R_TYPE_SEL.2, SJ1.2
unnamed: EPD_C10.2, J1.22
unnamed: EPD_C12.2, J1.24
unnamed: C32.2, IC2.A2 (REG)
OUT+: IC2.A3 (OUT+), TP_OP.TP
OUT-: IC2.C3 (OUT-), TP_ON.TP
P0.13: C30.2, R5.1, SW_UP.2; also elsewhere on the board
P0.14: C31.2, R8.1, SW_ENT.2; also elsewhere on the board
P1.01: Q1.1 (G), R_PWR_EPD.1; also elsewhere on the board
P1.02: C29.1, R7.1, SW_DN.2; also elsewhere on the board
PREVGH: D5.1 (K), EPD_C9.2, J1.21
PREVGL: D2.2 (A), EPD_C11.2, J1.23
RESE: J1.3, Q3.2 (S), R1_EP_DR.2
SCK: J1.13; also elsewhere on the board
SCL: IC2.C1 (SCL), U3.7 (SCL); also elsewhere on the board
SDA: IC2.B2 (SDA), U3.8 (SDA); also elsewhere on the board
VBAT: C27.2, TP_VBAT.TP, U3.2 (CELL), U3.3 (VDD); also elsewhere on the board
VBUS: C42.1, C43.1, D3.5 (VBUS), J4.A4_B9 (VBUS), J4.A9_B4 (VBUS); also elsewhere on the board

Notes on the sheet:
DMG2305UX-7
E-Paper Drive Circuit
E-Paper Display Connector
Fuel Gauge
Haptic Driver
E-Paper & Peripherals
Drawn by: Clarisse Braviceanu Badea
USB C Connector & ESD Protection

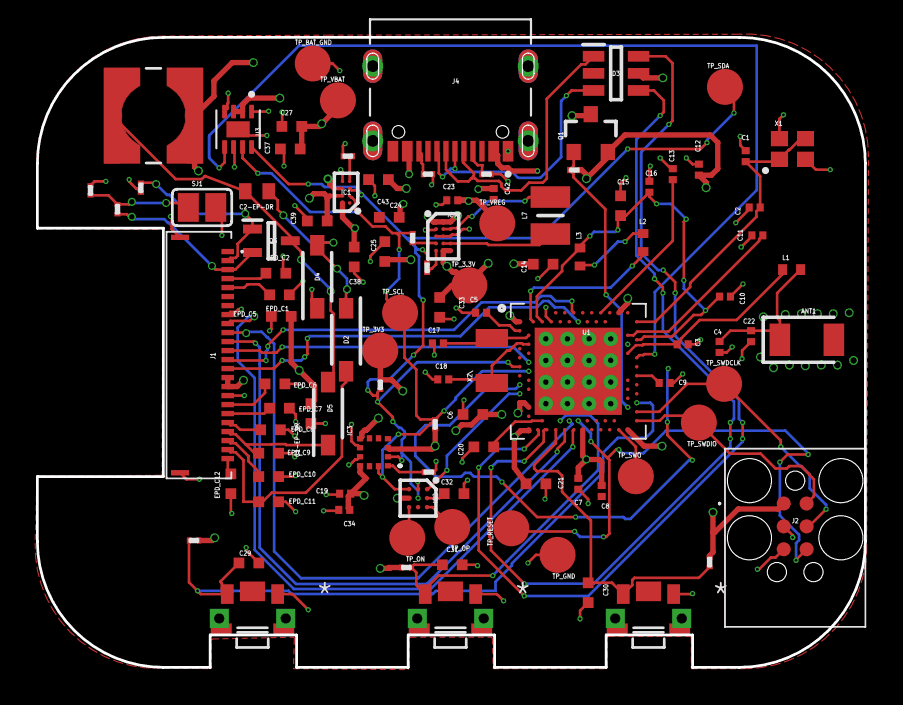
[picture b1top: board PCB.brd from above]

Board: 4 copper layers, 46.0 x 35.0 mm, 105 parts (0 on the bottom side), 66 nets.

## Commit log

2026-04-10 Added
2026-04-10 added licence
2026-04-21 updated project
2026-04-21 updated schematic.pdf
2026-04-21 added License
2026-04-22 Updated Schematic

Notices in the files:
parts and their libraries:
COPYRIGHT: Copyright (C) 2024 Ultra Librarian. All rights reserved.
